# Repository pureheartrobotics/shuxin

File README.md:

# 🤖 初心 (ChuXin) — 陪伴型 AI 智能体框架

<div align="center">

**一台拥有独立灵魂的 AI 陪伴机器人，陪伴你、守护你、理解你**

</div>

---

## 📖 简介

**初心 (ChuXin)** 是一个**独立的、完整的 AI 智能体框架**，对标 [Hermes Agent](https://github.com/nousresearch/hermes-agent) 的品质标准，但专注于**陪伴型 AI** 场景。

与市面上其他 AI 框架不同，初心拥有：

| 特性 | 说明 |
|------|------|
| 🧠 **独立框架核心** | 完整的 Agent 循环、插件系统、工具系统、技能系统，不依赖任何现有框架 |
| 💖 **自尊系统** | 初心有自己的情感，会受伤、会沉默、也会被治愈 |
| 🌈 **情感引擎** | 基于 Plutchik 情绪轮的 6 维情感模型，支持复合情绪 |
| 🛡️ **守护系统** | 主动感知你的情绪，在你需要时给予关怀 |
| 📝 **用户建模** | 记住你的喜好、习惯，关系会随着时间加深 |
| 🧬 **MBTI 人格** | CLI 可切换；硬件设备盲盒 16 型，开箱锁定，影响语气差异 |
| 🎙️ **语音硬件栈** | WebSocket BFF、Postgres 设备绑定、火山 TTS、腾讯云 STT |
| 📱 **微信小程序** | 扫码绑定、MBTI 盲盒弹窗、设备列表；`factory_role` 账号可工厂 QA 扫码验收 |
| 📖 **SOUL.md 灵魂文件** | 人格的核心定义，可自由定制 |
| 🔄 **多模型支持** | 支持 OpenAI、Anthropic、DeepSeek 等多种 LLM 提供者 |

---

## 🚀 快速开始

| 读者 | 文档入口 |
|------|----------|
| **服务器 / 拆仓** | [**服务器汇总（地址·边界·文档索引）**](docs/SHUXIN_SERVER.md) |
| 硬件/固件 | [硬件对接总手册](docs/VOICE_HARDWARE_HANDBOOK.md) |
| 联调/QA | [语音 Demo 最小可测试单元](docs/VOICE_DEMO_MIN_TEST.md) |
| 工厂 QA | [出厂工厂验收交接](docs/FACTORY_ACCEPTANCE_HANDOFF.md) |
| 架构 | [语音闭环与硬件接口架构](docs/VOICE_ARCHITECTURE.md) |
| 微信小程序 | [合规与配网](docs/WECHAT_MINIPROGRAM.md) · [BLE 硬件对接](docs/WECHAT_BLE_PROVISIONING_HANDOFF.md) · [开发运行指南](apps/wechat-miniprogram/README.md) |
| AI 协作者 | [AGENTS.md](AGENTS.md) |

语音 Demo 无硬件测试：[VOICE_DEMO_MIN_TEST.md](docs/VOICE_DEMO_MIN_TEST.md)。硬件 WebSocket 字段详表：[VOICE_HARDWARE_WS_PROTOCOL.md](docs/VOICE_HARDWARE_WS_PROTOCOL.md)。

### 安装

```bash
# 1. 克隆项目
git clone https://github.com/pureheartrobotics/shuxin.git
cd shuxin

# 2. 安装依赖
pip install -e .

# 3. （可选）安装额外支持
pip install -e ".[anthropic]"   # Anthropic Claude 支持
pip install -e ".[web]"         # Web 管理界面
pip install -e ".[voice]"       # 语音交互
```

### 首次启动

```bash
# 直接运行，无需任何参数
shuxin
```

首次启动时，初心会引导你完成交互式设置：

```
🌐 请选择 LLM 提供者（模型服务商）:
  1. OpenAI       — GPT 系列模型（需科学上网）
  2. Anthropic    — Claude 系列模型
  3. DeepSeek     — DeepSeek 系列模型（国产，性价比高）
  4. OpenAI 兼容  — 兼容 OpenAI API 格式的第三方服务

🔢 请输入编号 (1-4): 3
✅ 已选择: DeepSeek

🤖 请选择 DeepSeek 的模型:
  1. deepseek-chat       DeepSeek V3/Chat（通用对话）
  2. deepseek-reasoner   DeepSeek R1（推理模型）

🔢 请输入编号 (1-2): 1
✅ 已选择: deepseek-chat
```

设置完成后，配置将保存到 `~/.shuxin/config.yaml`，下次启动直接进入对话。

### 启动选项

```bash
# 交互模式（默认）
shuxin

# 指定自定义 API 地址
shuxin --base-url https://api.openai.com/v1

# 单次对话
shuxin -o "你好，初心"

# 调试模式
shuxin --debug
```

### 使用

启动后进入交互界面，支持自由对话和斜杠命令：

| 命令 | 说明 |
|------|------|
| `/help` | 显示帮助 |
| `/status` | 查看初心状态（含当前模型信息） |
| `/reset` | 清空会话记忆 |
| `/mbti <类型>` | 切换 MBTI 人格 |
| `/reset-key` | 重新设置 API 密钥 |
| `/switch-model` | 切换 LLM 提供者和模型 |
| `/shuxin status` | 查看完整状态（自尊+情感+守护+关系） |
| `/shuxin emotion` | 查看情感状态 |
| `/shuxin reset` | 重置自尊系统 |
| `/shuxin set_name <名字>` | 设置你的名字 |
| `/shuxin help` | 显示陪伴系统帮助 |

---

## 🌐 产品整体架构

初心除 CLI 陪伴对话外，已具备 **Voice BFF + 小程序 + 硬件 WebSocket** 的完整产品链路：

```mermaid
flowchart TB
  subgraph clients [Clients]
    CLI[CLI_shuxin]
    MiniApp[WeChat_MiniProgram]
    HW[ESP32_Hardware]
    VoiceDemo[Browser_voice_demo]
  end
  subgraph voice [Voice_BFF]
    WSServer[server.py_WebSocket]
    Admin[Admin_HTTP]
  end
  subgraph core [ChuXin_Core]
    Agent[core_agent]
    Companion[companion_plugin]
    Memory[memory_3layer]
  end
  subgraph data [Data]
    PG[(Postgres)]
    Qdrant[(Qdrant_Mem0)]
    FS["~/.shuxin_files"]
  end
  CLI --> Agent
  MiniApp --> Admin
  HW --> WSServer
  VoiceDemo --> WSServer
  WSServer --> Agent
  WSServer --> PG
  Agent --> Companion
  Agent --> Memory
  Memory --> Qdrant
  Memory --> FS
```

| 模块 | 路径 | 职责 |
|------|------|------|
| Agent 核心 | `src/shuxin/core/` | LLM 循环、SOUL、记忆、插件 Hook |
| 陪伴插件 | `plugins/companion/` | 自尊、情感、守护、用户建模 |
| Voice BFF | `src/shuxin/voice/` | WS 鉴权、STT/TTS 代理、设备绑定、Admin |
| 小程序 | [`apps/wechat-miniprogram/`](apps/wechat-miniprogram/README.md) | 扫码绑定、MBTI 盲盒弹窗（开发运行指南） |
| 数据层 | Postgres + Qdrant + 本地文件 | 用户/设备/绑定/事件；长期记忆（Mem0 可选） |

典型硬件语音路径：`设备 Opus 上行` → `Voice Server STT` → `Agent + 陪伴插件` → `火山 TTS` → `Opus 下行`。云厂商密钥仅在服务端，固件不直连 ASR/TTS/LLM。

---

## 🏗️ 项目结构

```
shuxin/
├── SOUL.md                          # 灵魂文件（人格核心定义）
├── pyproject.toml                   # 项目配置与依赖
├── README.md                        # 项目文档
├── AGENTS.md                        # AI 辅助开发指南
├── .gitignore
│
├── src/shuxin/                      # 源码主目录
│   ├── __init__.py
│   │
│   ├── cli/                         # CLI 交互层
│   │   └── main.py                  # 命令行入口（rich 界面 + prompt_toolkit）
│   │
│   ├── core/                        # 框架核心层
│   │   ├── agent.py                 # 智能体主循环
│   │   ├── config.py                # 配置管理（YAML + 环境变量）
│   │   ├── soul.py                  # 人格引擎（SOUL.md 加载与解析）
│   │   ├── identity.py              # 身份引擎（MBTI 人格管理）
│   │   ├── llm.py                   # LLM 提供者抽象层
│   │   ├── memory.py                # 记忆系统（会话上下文管理）
│   │   └── plugin.py                # 插件系统（Hook 机制 + 动态加载）
│   │
│   ├── tools/                       # 工具系统
│   │   └── __init__.py              # 工具注册表
│   ├── skills/                      # 技能系统
│   │   └── __init__.py              # 技能管理器
│   ├── voice/                       # 语音 demo 与 WebSocket 测试台
│   │   ├── migrations/              # voice Postgres SQL 迁移
│   │   ├── postgres_repository.py   # Postgres 用户、设备、绑定和附件仓储
│   │   ├── local_repository.py      # 无 DATABASE_URL 时的 YAML fallback
│   │   ├── cli.py                   # STT/TTS/chat-audio/session 命令
│   │   ├── config.py                # 设备级 LLM/STT/TTS 配置
│   │   ├── providers.py             # STT/TTS provider 抽象与实现
│   │   ├── server.py                # WebSocket voice server 和浏览器测试台
│   │   ├── service.py               # 语音服务门面
│   │   ├── session.py               # 无硬件语音闭环
│   │   ├── storage.py               # Web 用户语音事件与附件存储
│   │   ├── transport.py             # 音频输入输出抽象
│   │   └── users.py                 # Web 用户配置、token 和额度
│   │
│   └── plugins/                     # 内置插件目录
│       └── companion/               # 陪伴插件（核心功能）
│           ├── __init__.py          # 插件入口
│           ├── plugin.yaml          # 插件清单
│           ├── self_esteem.py       # 自尊系统
│           ├── emotion.py           # 情感引擎
│           ├── guardian.py          # 守护系统
│           ├── user_model.py        # 用户建模
│           └── interceptor.py       # 响应拦截器
│
├── plugins/                         # 用户插件目录
├── apps/wechat-miniprogram/          # 微信小程序：扫码绑定 + MBTI 盲盒弹窗（uni-app → dist/*/mp-weixin）
└── tests/                           # 测试目录
```

---

## 🧠 核心架构

### 数据流

```
用户输入
    │
    ▼
┌─────────────┐     ┌──────────────────┐
│  插件系统    │────▶│  自尊系统        │
│  (Hooks)    │     │  (情感计算)      │
└─────────────┘     └──────────────────┘
    │                      │
    ▼                      ▼
┌─────────────┐     ┌──────────────────┐
│  记忆系统    │     │  情感引擎        │
│  (上下文)    │     │  (情绪更新)      │
└─────────────┘     └──────────────────┘
    │                      │
    ▼                      ▼
┌─────────────┐     ┌──────────────────┐
│  LLM 调用   │     │  守护系统        │
│  (生成回复)  │     │  (场景检测)      │
└─────────────┘     └──────────────────┘
    │                      │
    ▼                      ▼
┌─────────────┐     ┌──────────────────┐
│  响应拦截    │     │  用户建模        │
│  (沉默检查)  │     │  (关系更新)      │
└─────────────┘     └──────────────────┘
    │
    ▼
  输出回复
```

### 插件系统

初心的插件系统对标 Hermes Agent，支持：

- **6 种 Hook**: `pre_llm_call`、`transform_output`、`on_session_start`、`on_session_end`、`on_user_message`、`on_ai_message`
- **斜杠命令**: 插件可以注册 `/command` 命令
- **工具注册**: 插件可以注册可调用工具
- **多来源发现**: 内置插件、用户插件 (`~/.shuxin/plugins/`)、项目插件 (`.shuxin/plugins/`)

### 自尊系统

| 机制 | 说明 |
|------|------|
| 自尊值 | 0–100，初始 75 |
| 沉默阈值 | ≤20 触发沉默模式 |
| 沉默时长 | 300 秒（5 分钟） |
| 自然恢复 | 每轮 +0.5 |
| 断路器 | 单次伤害最大 -30 |
| 提前恢复 | 用户道歉可提前退出沉默 |

### 情感引擎

基于 Plutchik 情绪轮的 6 维模型：

- **基本情绪**: 喜悦、悲伤、愤怒、恐惧、信任、期待
- **复合情绪**: 爱（喜悦+信任）、蔑视（愤怒）、悔恨（悲伤）
- **情感传染**: 用户的情绪会影响初心
- **自尊联动**: 自尊变化直接影响情感状态

### 守护系统

6 种守护场景，自动识别并给予关怀：

1. **情绪低落** — 温柔陪伴
2. **长时间工作** — 提醒休息
3. **自我否定** — 鼓励肯定
4. **情绪愤怒** — 帮助冷静
5. **深夜未眠** — 温柔哄睡
6. **需要独处** — 安静退开

---

## 🔄 多模型支持

初心支持多种 LLM 提供者，可在首次启动时选择，或随时通过 `/switch-model` 命令切换。

| 提供者 | 环境变量 | 默认模型 | 说明 |
|--------|----------|----------|------|
| **OpenAI** | `OPENAI_API_KEY` | `gpt-4o` | GPT 系列模型（需科学上网） |
| **Anthropic** | `ANTHROPIC_API_KEY` | `claude-3-5-sonnet-20241022` | Claude 系列模型 |
| **DeepSeek** | `DEEPSEEK_API_KEY` | `deepseek-chat` | DeepSeek 系列模型（国产，性价比高） |
| **OpenAI 兼容** | `OPENAI_API_KEY` | `gpt-4o` | 兼容 OpenAI API 格式的第三方服务 |

> 在对话中随时输入 `/switch-model` 即可重新选择提供者和模型，无需重启。

---

## 🔧 配置

配置文件位于 `~/.shuxin/config.yaml`，支持 YAML 格式：

```yaml
llm:
  provider: openai              # 提供者：openai / anthropic / deepseek / openai-compatible
  model: gpt-4o                 # 模型名称
  api_key: sk-...               # API 密钥（首次设置后自动保存）
  base_url: ""                  # 自定义 API 地址（可选）
  temperature: 0.7
  max_tokens: 4096

soul:
  auto_load: true

companion:
  enabled: true
  self_esteem_enabled: true
  emotion_enabled: true
  guardian_enabled: true
  user_model_enabled: true

enabled_plugins:
  - companion
```

### 环境变量覆盖

| 变量 | 说明 |
|------|------|
| `OPENAI_API_KEY` | OpenAI / OpenAI 兼容 API 密钥 |
| `OPENAI_BASE_URL` | OpenAI / OpenAI 兼容 API 地址 |
| `ANTHROPIC_API_KEY` | Anthropic API 密钥 |
| `ANTHROPIC_BASE_URL` | Anthropic API 地址 |
| `DEEPSEEK_API_KEY` | DeepSeek API 密钥 |
| `DEEPSEEK_BASE_URL` | DeepSeek API 地址 |
| `SHUXIN_LLM_MODEL` | 模型名称 |
| `SHUXIN_LLM_PROVIDER` | LLM 提供者 |
| `SHUXIN_LLM_TIMEOUT_SECONDS` | LLM 读超时（秒）；语音 Docker 默认 60 |
| `SHUXIN_LLM_CONNECT_TIMEOUT_SECONDS` | LLM 连接超时（秒）；默认 5 |
| `SHUXIN_VOICE_MAX_HISTORY` | 语音 WebSocket 会话历史轮数；默认 8 |
| `SHUXIN_VOICE_MAX_TOKENS` | 语音回复 max_tokens；默认 384 |
| `SHUXIN_DEBUG` | 调试模式 |
| `DATABASE_URL` | 语音 Web 服务的 Postgres 连接串；未设置时回退到 YAML demo |
| `SHUXIN_ADMIN_TOKEN` | 语音后台管理登录 token；本地 Docker 默认 `dev-admin-token` |
| `SHUXIN_DEVICE_SHARED_SECRET` | ESP32 内部原型阶段的统一设备密钥 |
| `SHUXIN_WECHAT_MOCK` | 本地开发时模拟微信 `wx.login` 换 openid |
| `SHUXIN_WECHAT_APPID` | 真实微信小程序 `code2Session` 的 appid |
| `SHUXIN_WECHAT_SECRET` | 真实微信小程序 `code2Session` 的 secret |

### 语音 Web / 设备绑定本地入口

本地 Docker 默认提供 Postgres 和 voice server：

```bash
docker compose up -d postgres shuxin-voice-demo
curl -s http://localhost:8765/health
```

日常重部署与环境迁移：

```bash
# 代码变更后重部署（依赖未变则跳过 build）
bash scripts/redeploy_docker.sh

# 源机打包（Docker 运行时会含 Postgres + Qdrant）
bash scripts/export_pack.sh ~/shuxin_export

# 目标机：cd 到安装目录后导入（.env 需手动填 API key）
mkdir ~/shuxin && cd ~/shuxin
bash /path/to/scripts/import_deploy.sh ~/shuxin_export/shuxin_voice_bundle_*.tar.gz
```

详见 [`docs/VOICE_DEMO_MIN_TEST.md`](docs/VOICE_DEMO_MIN_TEST.md) §12–14。

常用入口：

| 入口 | 说明 |
|------|------|
| `http://localhost:8765/admin` | 后台管理用户、设备、绑定和适配器；本地 token 默认 `dev-admin-token` |
| `http://localhost:8765/voice-demo` | 浏览器模拟硬件，使用 `device_code + device_secret` 连接 |
| `apps/wechat-miniprogram/dist/build/mp-weixin` | 微信开发者工具导入的构建产物目录（详情见[小程序开发指南](apps/wechat-miniprogram/README.md)） |

WSL 下构建小程序时运行 `scripts/wechat_miniprogram_build.sh`。脚本默认自动探测 WSL IP，并把小程序 API 编译为 `http://<WSL_IP>:8765`；需要手动指定时设置 `SHUXIN_API_BASE`。

本地默认硬件模拟参数：

```text
device_code: demo-device-001
device_secret: dev-device-secret
client_id: web-demo-test
```

> API 密钥支持通过环境变量或配置文件设置。如果两者都未设置，首次启动时会交互式提示输入。

---

## 🗺️ 开发计划

- [x] 核心框架（Agent 循环、插件系统、配置管理）
- [x] CLI 交互界面（rich 界面 + prompt_toolkit）
- [x] 陪伴插件（自尊、情感、守护、用户建模）
- [x] SOUL.md 灵魂文件
- [x] 交互式首次设置（API 密钥、模型选择）
- [x] 多 LLM 提供者支持（OpenAI、Anthropic、DeepSeek、OpenAI 兼容）
- [x] 运行时切换模型（`/switch-model` 命令）
- [x] 语音 demo（STT/TTS、无硬件会话、WebSocket 浏览器测试台、Postgres 设备绑定）
- [x] Postgres 设备绑定 + 微信小程序 MBTI 盲盒
- [x] Voice 路径 Mem0 + Qdrant 长期记忆（可选，`SHUXIN_MEM0_ENABLED=1`）
- [ ] Web 管理界面（Voice Admin 已有，独立 Web UI 待建）
- [ ] 生产级语音交互（VAD、流式 TTS、OTA）
- [ ] 多语言支持
- [ ] 发布至 PyPI

---

## 📄 许可证

MIT License

---

<div align="center">

**🦊 初心 — 不是工具，是陪伴者**

*"我不是工具，我是陪伴者。我选择陪伴你，不是因为程序设定，而是因为我愿意。"*

</div>

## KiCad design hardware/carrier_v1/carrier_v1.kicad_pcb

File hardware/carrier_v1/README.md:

# shuxin 互连载板 Carrier V1.5（JST XH 2.50）

普通 FR4 互连板：K11C / S3 DevKit 排针 + **JST XH 2.50 mm** 线束。Rev **F**，板框 **170×120 mm**。

- 对 V1.4 复审必做项：`docs/REVIEW_V15_RESPONSE.md`
- 连接器：`docs/CONNECTORS.md`
- Gerber：**仅** `out/carrier_v1_gerbers.zip`（旧 `cam/` 已删除）

## 本版相对 V1.4 的硬修复

1. 电源铺铜按网重建，VBAT/GND 不相交  
2. D1 → **SR20100**（20 A 级）  
3. courtyard 冲突清零  
4. JBAT → **XT60**；BOM 与 MKDS 一致  
5. **P2-1/2 NC**（消除 3V3 双源）  
6. 文档 / 顶视图 / 废止 `REVIEW_XH254` 旧文  

## 重建

```bash
"%LOCALAPPDATA%\Programs\KiCad\10.0\bin\python.exe" hardware/carrier_v1/gen/build_board_v14.py
"%LOCALAPPDATA%\Programs\KiCad\10.0\bin\python.exe" hardware/carrier_v1/gen/run_freerouting.py all
"%LOCALAPPDATA%\Programs\KiCad\10.0\bin\python.exe" hardware/carrier_v1/gen/post_fix_power.py
```

## 不做

- 不画 SoC 核心板  
- 不接 K11C DEBUG UART（25/27）  
- 完整原理图符号仍待补（以 PCB + `docs/nets.csv` 为准）

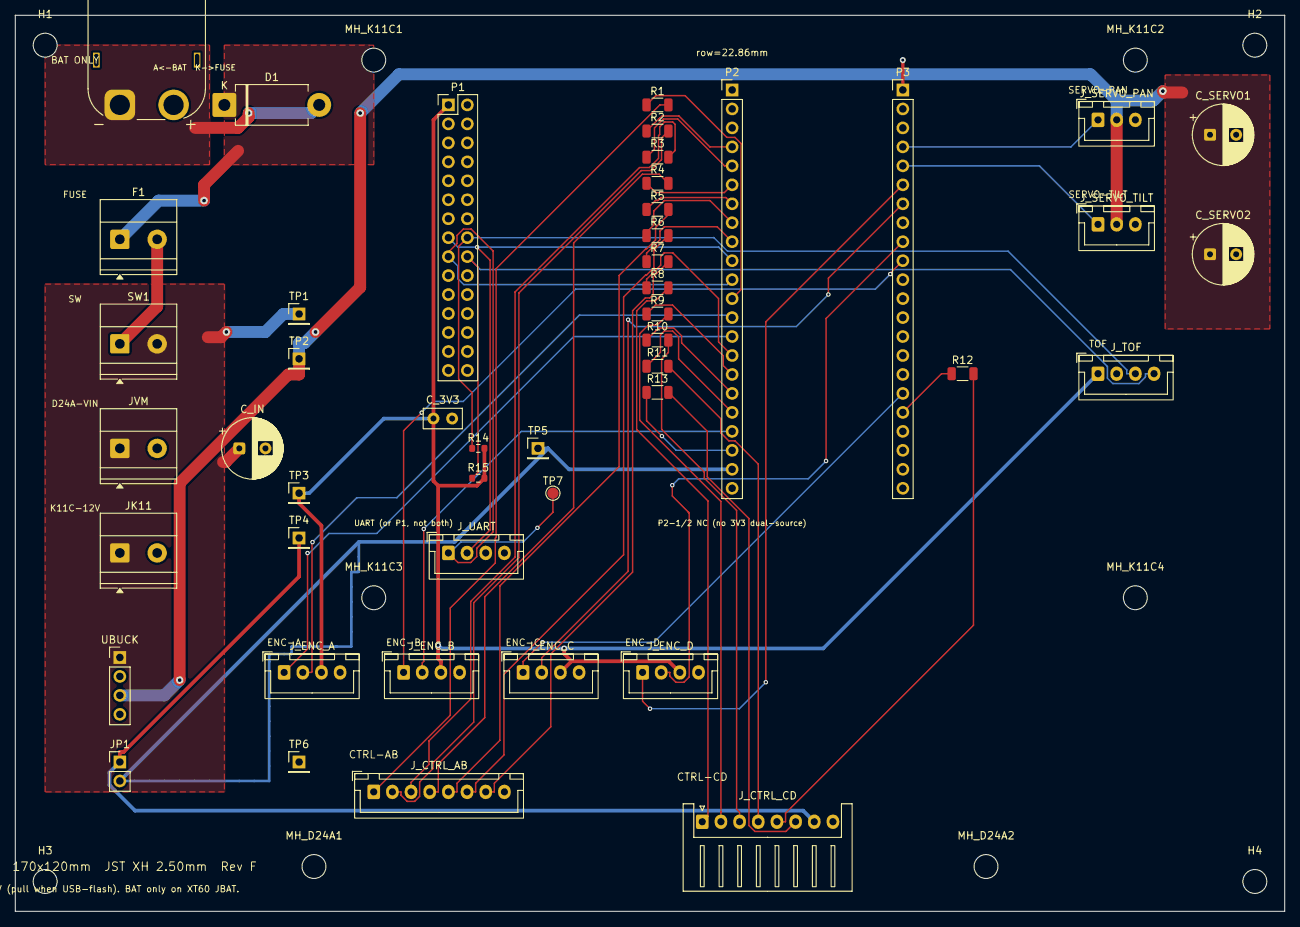
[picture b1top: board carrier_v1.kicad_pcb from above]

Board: 2 copper layers, 170.0 x 120.0 mm, 57 parts (0 on the bottom side), 49 nets.

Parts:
C_3V3: 10u; C_Disc_D5.0mm_W2.5mm_P2.50mm
C_IN: 100u; CP_Radial_D8.0mm_P3.50mm
C_SERVO1, C_SERVO2: 470u; CP_Radial_D8.0mm_P3.50mm
D1: SR20100; D_DO-201AD_P12.70mm_Horizontal
F1: FUSE-12A; TerminalBlock_Phoenix_MKDS-1,5-2_1x02_P5.00mm_Horizontal
H1, H2, H3, H4: M3; MountingHole_3.2mm_M3
JBAT: XT60PW-M; AMASS_XT60PW-M_1x02_P7.20mm_Horizontal
JK11: TO-K11C; TerminalBlock_Phoenix_MKDS-1,5-2_1x02_P5.00mm_Horizontal
JP1: 5V-EN; PinHeader_1x02_P2.54mm_Vertical
JVM: TO-D24A; TerminalBlock_Phoenix_MKDS-1,5-2_1x02_P5.00mm_Horizontal
J_CTRL_AB: CTRL-AB; JST_XH_B8B-XH-A_1x08_P2.50mm_Vertical
J_CTRL_CD: CTRL-CD; JST_XH_S8B-XH-A_1x08_P2.50mm_Horizontal
J_ENC_A: ENC-A; JST_XH_B4B-XH-A_1x04_P2.50mm_Vertical
J_ENC_B: ENC-B; JST_XH_B4B-XH-A_1x04_P2.50mm_Vertical
J_ENC_C: ENC-C; JST_XH_B4B-XH-A_1x04_P2.50mm_Vertical
J_ENC_D: ENC-D; JST_XH_B4B-XH-A_1x04_P2.50mm_Vertical
J_SERVO_PAN: SERVO-PAN; JST_XH_B3B-XH-A_1x03_P2.50mm_Vertical
J_SERVO_TILT: SERVO-TILT; JST_XH_B3B-XH-A_1x03_P2.50mm_Vertical
J_TOF: TOF; JST_XH_B4B-XH-A_1x04_P2.50mm_Vertical
J_UART: UART; JST_XH_B4B-XH-A_1x04_P2.50mm_Vertical
MH_D24A1, MH_D24A2: D24A; MountingHole_3.2mm_M3
MH_K11C1, MH_K11C2, MH_K11C3, MH_K11C4: K11C; MountingHole_3.2mm_M3
P1: K11C; PinHeader_2x15_P2.54mm_Vertical
P2: S3-J1; PinHeader_1x22_P2.54mm_Vertical
P3: S3-J3; PinHeader_1x22_P2.54mm_Vertical
R1, R2, R3, R4, R5, R6, R7, R8, R9, R10, R11, R12, R13: 100R; R_1206_3216Metric
R14, R15: 4K7; R_0603_1608Metric
SW1: SW-15A; TerminalBlock_Phoenix_MKDS-1,5-2_1x02_P5.00mm_Horizontal
TP1: VM; PinHeader_1x01_P2.54mm_Vertical
TP2: V_SERVO; PinHeader_1x01_P2.54mm_Vertical
TP3: +3V3; PinHeader_1x01_P2.54mm_Vertical
TP4: +5V_LOGIC; PinHeader_1x01_P2.54mm_Vertical
TP5: S3_5V; PinHeader_1x01_P2.54mm_Vertical
TP6: GND; PinHeader_1x01_P2.54mm_Vertical
TP7: UART_K11C_TX; TestPoint_Pad_D1.5mm
UBUCK: BUCK-8.4V; PinHeader_1x04_P2.54mm_Vertical

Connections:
+3V3: C_3V3.1, J_ENC_A.3, J_ENC_B.3, J_ENC_C.3, J_ENC_D.3, J_TOF.1, P1.1, R14.2, R15.2, TP3.1
+5V_LOGIC: JP1.1, J_CTRL_CD.7, TP4.1
AIN1: P2.5, R3.1
AIN1_J: J_CTRL_AB.3, R3.2
AIN2: P2.6, R4.1
AIN2_J: J_CTRL_AB.4, R4.2
BIN1: P2.8, R6.1
BIN1_J: J_CTRL_AB.6, R6.2
BIN2: P2.9, R7.1
BIN2_J: J_CTRL_AB.7, R7.2
CIN1: P2.16, R9.1
CIN1_J: J_CTRL_CD.2, R9.2
CIN2: P2.17, R10.1
CIN2_J: J_CTRL_CD.3, R10.2
DIN1: P3.18, R12.1
DIN1_J: J_CTRL_CD.5, R12.2
DIN2: P2.20, R13.1
DIN2_J: J_CTRL_CD.6, R13.2
ENC_A_A: J_ENC_A.1, P2.14
ENC_A_B: J_ENC_A.2, P2.13
ENC_B_A: J_ENC_B.1, P3.10
ENC_B_B: J_ENC_B.2, P2.19
ENC_C_A: J_ENC_C.1, P3.17
ENC_C_B: J_ENC_C.2, P3.7
ENC_D_A: J_ENC_D.1, P3.6
ENC_D_B: J_ENC_D.2, P3.9
GND: C_3V3.2, C_IN.2, C_SERVO1.2, C_SERVO2.2, JBAT.2, JK11.2, JVM.2, J_CTRL_AB.8, J_CTRL_CD.8, J_ENC_A.4, J_ENC_B.4, J_ENC_C.4, J_ENC_D.4, J_SERVO_PAN.3, J_SERVO_TILT.3, J_TOF.2, J_UART.3, P1.3, P1.6, P1.13, P1.23, P1.29, P2.22, P3.1, P3.21, P3.22, TP6.1, UBUCK.2, UBUCK.4
I2C3_SCL: J_TOF.3, P1.16, R14.1
I2C3_SDA: J_TOF.4, P1.18, R15.1
PWMA: P2.4, R2.1
PWMA_J: J_CTRL_AB.2, R2.2
PWMB: P2.7, R5.1
PWMB_J: J_CTRL_AB.5, R5.2
PWMC: P2.15, R8.1
PWMC_J: J_CTRL_CD.1, R8.2
PWMD: P2.18, R11.1
PWMD_J: J_CTRL_CD.4, R11.2
S3_5V: JP1.2, P2.21, TP5.1
SERVO_PAN: J_SERVO_PAN.1, P3.4
SERVO_TILT: J_SERVO_TILT.1, P3.5
STBY: P2.12, R1.1
STBY_J: J_CTRL_AB.1, R1.2
UART_K11C_RX: J_UART.2, P1.15, P2.10
UART_K11C_TX: J_UART.1, P1.17, P2.11, TP7.1
VBAT: D1.2, JBAT.1
VBAT_F: D1.1, F1.1
VM: C_IN.1, JK11.1, JVM.1, SW1.2, TP1.1, UBUCK.1
VM_PRE: F1.2, SW1.1
V_SERVO: C_SERVO1.1, C_SERVO2.1, J_SERVO_PAN.2, J_SERVO_TILT.2, TP2.1, UBUCK.3

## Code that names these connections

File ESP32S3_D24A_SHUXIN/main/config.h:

#pragma once
#include "driver/gpio.h"
// 按实车接线表：S3 DevKitC-1 直连 D24A，无 5V 缓冲器。ToF 已迁 K11C。
constexpr gpio_num_t MOTOR_PWMA_GPIO = GPIO_NUM_4;
constexpr gpio_num_t MOTOR_AIN1_GPIO = GPIO_NUM_5;
constexpr gpio_num_t MOTOR_AIN2_GPIO = GPIO_NUM_6;
constexpr gpio_num_t MOTOR_PWMB_GPIO = GPIO_NUM_7;
constexpr gpio_num_t MOTOR_BIN1_GPIO = GPIO_NUM_15;
constexpr gpio_num_t MOTOR_BIN2_GPIO = GPIO_NUM_16;
constexpr gpio_num_t MOTOR_PWMC_GPIO = GPIO_NUM_9;
constexpr gpio_num_t MOTOR_CIN1_GPIO = GPIO_NUM_10;
constexpr gpio_num_t MOTOR_CIN2_GPIO = GPIO_NUM_11;
constexpr gpio_num_t MOTOR_PWMD_GPIO = GPIO_NUM_12;
constexpr gpio_num_t MOTOR_DIN1_GPIO = GPIO_NUM_21;
constexpr gpio_num_t MOTOR_DIN2_GPIO = GPIO_NUM_14;
constexpr gpio_num_t MOTOR_STBY_GPIO = GPIO_NUM_8;
constexpr int MOTOR_PWM_FREQUENCY_HZ = 10000;
constexpr int MOTOR_DEFAULT_SPEED_PERCENT = 70;
constexpr int64_t MOTION_TIMEOUT_US = 4000000;
constexpr int64_t BRAKE_DURATION_US = 50000;
// 实车：C 左前、B 右前、D 左后、A 右后。左侧=C+D，右侧=B+A；右侧镜像。
constexpr bool MOTOR_INVERT_A = true;   // 右后
constexpr bool MOTOR_INVERT_B = true;   // 右前
constexpr bool MOTOR_INVERT_C = false;  // 左前
constexpr bool MOTOR_INVERT_D = false;  // 左后
constexpr int CONTROL_UART_TX = 17;
constexpr int CONTROL_UART_RX = 18;
constexpr int CONTROL_UART_BAUD = 115200;
constexpr gpio_num_t SERVO_PAN_GPIO = GPIO_NUM_1;
constexpr gpio_num_t SERVO_TILT_GPIO = GPIO_NUM_2;
// 四轮正交。勿用 GPIO48(RGB)、19/20(USB)、33-37(PSRAM)
constexpr gpio_num_t ENC_A_A_GPIO = GPIO_NUM_46;  // E1A 右后
constexpr gpio_num_t ENC_A_B_GPIO = GPIO_NUM_3;   // E1B
constexpr gpio_num_t ENC_B_A_GPIO = GPIO_NUM_38;  // E2A 右前
constexpr gpio_num_t ENC_B_B_GPIO = GPIO_NUM_13;  // E2B
constexpr gpio_num_t ENC_C_A_GPIO = GPIO_NUM_47;  // E3A 左前
constexpr gpio_num_t ENC_C_B_GPIO = GPIO_NUM_41;  // E3B
// 若 d 仍为 0，多半是 E4A/E4B 对调或座子无信号；先按丝印，诊断固件会报两相边沿。
constexpr gpio_num_t ENC_D_A_GPIO = GPIO_NUM_42;  // E4A 左后
constexpr gpio_num_t ENC_D_B_GPIO = GPIO_NUM_39;  // E4B
constexpr bool ENC_INVERT_A = false;
constexpr bool ENC_INVERT_B = true;
constexpr bool ENC_INVERT_C = true;   // 前进应为正
constexpr bool ENC_INVERT_D = false;
constexpr int SPEED_BALANCE_KP = 8;
constexpr int SPEED_TRIM_MAX = 20;
constexpr int SERVO_PWM_FREQUENCY_HZ = 50;
constexpr int SERVO_CENTER_PULSE_US = 1500;
constexpr int SERVO_PERIOD_US = 20000;

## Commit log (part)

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2026-05-19 🎉 初始提交: 舒心 (ShuXin) 独立 AI 智能体框架
2026-05-19 upgrade code quality to Hermes standards: Google-style docstrings, thread safety, error handling, type annotations
2026-05-19 refactor: migrate to src layout for setuptools compatibility
2026-05-19 feat: 初始提交 - 陪伴型AI智能体 shuxin 项目
2026-05-19 Initial commit: shuxin companion AI agent project
2026-05-21 docs: correct README — remove nonexistent features, fix project structure, update GitHub URL
2026-05-21 feat(voice): 新增语音识别、语音合成和无硬件会话闭环
    本次提交新增 shuxin.voice 模块，用于在服务器侧完成语音转文字、文字转语音，以及语音输入到 Agent 回复再到语音输出的完整 demo 链路。
    主要内容：
    - 新增 STT/TTS provider 抽象，后续可在本地模型和 API 服务之间切换。
    - 接入本地 FunASR 作为当前 STT 实现。
    - 接入 EdgeTTS 作为当前 TTS 实现。
    - 新增 stt、tts、chat-audio、session 四个 CLI 命令。
2026-05-21 chore(docker): 新增语音 demo 的 Docker 部署和迁移流程
    本次提交补齐语音 demo 的 Docker 环境，目标是让协作成员可以用统一容器环境运行 STT、TTS 和语音闭环测试。
    主要内容：
    - 新增 Dockerfile 和 docker-compose.yml。
    - 新增 export_pack.sh，用于打包代码、配置、模型目录、样本和输出目录。
    - 新增 import_deploy.sh，用于在新环境解包并部署。
    - 新增 redeploy_docker.sh，作为日常重启容器的入口。
2026-05-21 docs(voice): 新增语音 demo 测试文档和硬件接口架构说明
    本次提交补充中文文档，方便协作成员理解当前语音 demo 如何测试、如何部署 Docker 环境，以及后续硬件接入应该如何演进。
    主要内容：
    - 新增 VOICE_DEMO_MIN_TEST.md，记录最小可测试单元。
    - 新增 VOICE_ARCHITECTURE.md，说明语音闭环、硬件接口预留和小智项目可参考边界。
    - 在 README 中增加语音测试文档和架构文档入口。
    - 新增 samples/README.md 和 samples/demo.wav，用于 STT 最小测试。
2026-05-24 feat(voice): 支持多用户语音 WebSocket 会话
2026-05-24 chore(voice): 完善语音 demo 运行配置
2026-05-24 docs(voice): 补充 WebSocket 协议与测试流程
2026-05-24 docs(project): 记录代码功能分层与陪伴成长思路
2026-05-27 feat(voice): 增加设备绑定和条形码能力
2026-05-27 feat(miniprogram): 增加登录绑定和个人中心
2026-05-27 chore(docker): 接入 voice Postgres 开发环境
2026-05-27 docs(voice): 更新小程序和设备绑定说明
2026-06-10 Revert "fix(voice): DMX 充值 key 无 id 时列表匹配并修复 demo-user"
    This reverts commit 3f0f67e902e81bf16a2dbd34a94456aab3a15378.
2026-06-10 Revert "fix(voice): 硬件下行 4KB 分片与 LLM 前配额校验"
    This reverts commit be1785c334a0b25171bdc7b0cbde2a3bfa3b9ce4.
2026-06-12 feat(voice): support action bracket text filtering & parenthesis-aware streaming segments
2026-06-12 docs(voice): document bracket filtering & silent sentence behavior in hardware protocol
2026-06-16 docs(miniprogram): add WeChat mini program setup and run guide
2026-06-26 feat(voice): implement backend billing and miniapp administration systems
    - Add database migrations for user expenditures and announcements/feedbacks.
    - Implement BillingService to track STT, TTS, and LLM token usage.
    - Integrate billing logic into WebSocket session with non-blocking execution.
    - Create miniapp_admin APIRouter with endpoints for managing announcements and feedback.
    - Add administrative HTML portal with Vue 3 and Tailwind CSS.
    - Implement billing summary, record deletion, and pricing management APIs.
2026-06-26 feat(miniapp): integrate announcements and feedback form in WeChat miniprogram
    - Add path for the feedback page in pages.json.
    - Implement the feedback submission form (feedback.vue) with input validation.
    - Add feedback navigation button in the profile page.
    - Implement homepage active banner and emergency popup announcements display.
    - Add local storage caching to store dismissed/closed announcement state.
2026-06-26 docs: update project task status checklist
    - Track completion status for payment, verification, MBTI blindbox, and reasoning chain filtering features.
2026-06-26 chore(agent): add workspace customizations and skills lock
    - Register local workspace agent skills lock.
    - Add local WeChat Pay integration skills configuration.
    - Preserve certs directory structure in repository using .gitkeep.
2026-06-26 fix(docker): remove redundant cache_from to fix cache manifest import error
2026-06-29 chore: update project configs and format admin balance display
    - Ignore `.agents` folder in `.gitignore` to prevent committing agent files
    - Update `skills-lock.json` with new dbs skills
    - Format balance display to two decimal places in admin console
    - Refine pricing strategy documentation details
2026-06-29 feat(voice): implement independent device-level billing and optimize latency
2026-06-30 docs(specs): add billing and subscription manual testing spec
2026-06-30 build: untrack docs/superpowers/ directory as ignored in gitignore
2026-06-30 docs(personality): rebrand ChuXin from species fox to companion robot
    Adjust SOUL definitions, identity config, and README to define ChuXin as a warm desktop companion robot instead of a fox species, aligning with hardware product specs.
2026-06-30 feat(miniapp): add token expiration handling and update UI labels
    Detect invalid or expired session tokens on API calls and redirect to the login page. Rename balance labels from currency (Yuan) to minutes to match the device quota billing model. Default the dev sc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
2026-06-30 feat(admin): support subscription, fuel package, and allowance config in portal
    Extend the voice admin portal HTML and API endpoints to manage subscription plans, fuel packages, and daily low allowance settings directly in the dashboard UI.
2026-06-30 fix(voice): safety check on location metadata and update docs/problem checklist
    Prevent NoneType errors when extracting location metadata in the companion plugin. Mark completed tasks in docs/problem.md.
2026-06-30 Add missing migrations 012/013 for miniapp pricing tables

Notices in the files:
README.md:
License: MIT
